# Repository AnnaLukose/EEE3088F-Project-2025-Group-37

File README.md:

# EEE3088F-Project-2025
Welcome to the repo for group 37's micromouse project!

The final design kicad files are available in the KICAD FILES folder.
Previous versions are also available in the draft 1 and draft 2 zip folders.

To view the schematic for our final design, view the Schematic pdf above.

This project required us to design a single PCB to fulfill the following power module requirements for a micromouse:

* Operate up to 4 motors bidirectionally with the pins available to you (listed in the power pinout
table). You will need to control 2x brushed DC motors which could each draw 200mA at the
highest voltage of a 1S1P battery (the battery is further specified in the battery section).
The other 2x motors are for the auxiliary connection and need to operate 500mA each.
* Place an INA219 for monitoring the battery on the I2C Bus and configure it correctly with
respect to the hardware (cannot have BOTH A0 AND A1 on GND)
* Charge the battery from the 9V input pin (listed in the power pinout table).
* Have two charging modes for a higher and lower charging current for the battery (200mA, and
approximately 600mA ±100mA from the battery perspective.
* Integrate USB C and get 9V out of the USB Host
* Provide 2x External Load Switching at 1A each (High Side connected to your 5V)
* Provide a 3V3 5% accuracy (300mA max) and 5V Out 5% accuracy (1.5A max)
* Provide an ON/OFF switch. OFF state: battery draw <30uA. ON state: can provide your robot
peak current of 2A. The switch needs to shut down 5V and 3V3

The requirements were split between us, each members files can be found under their corresponding name.

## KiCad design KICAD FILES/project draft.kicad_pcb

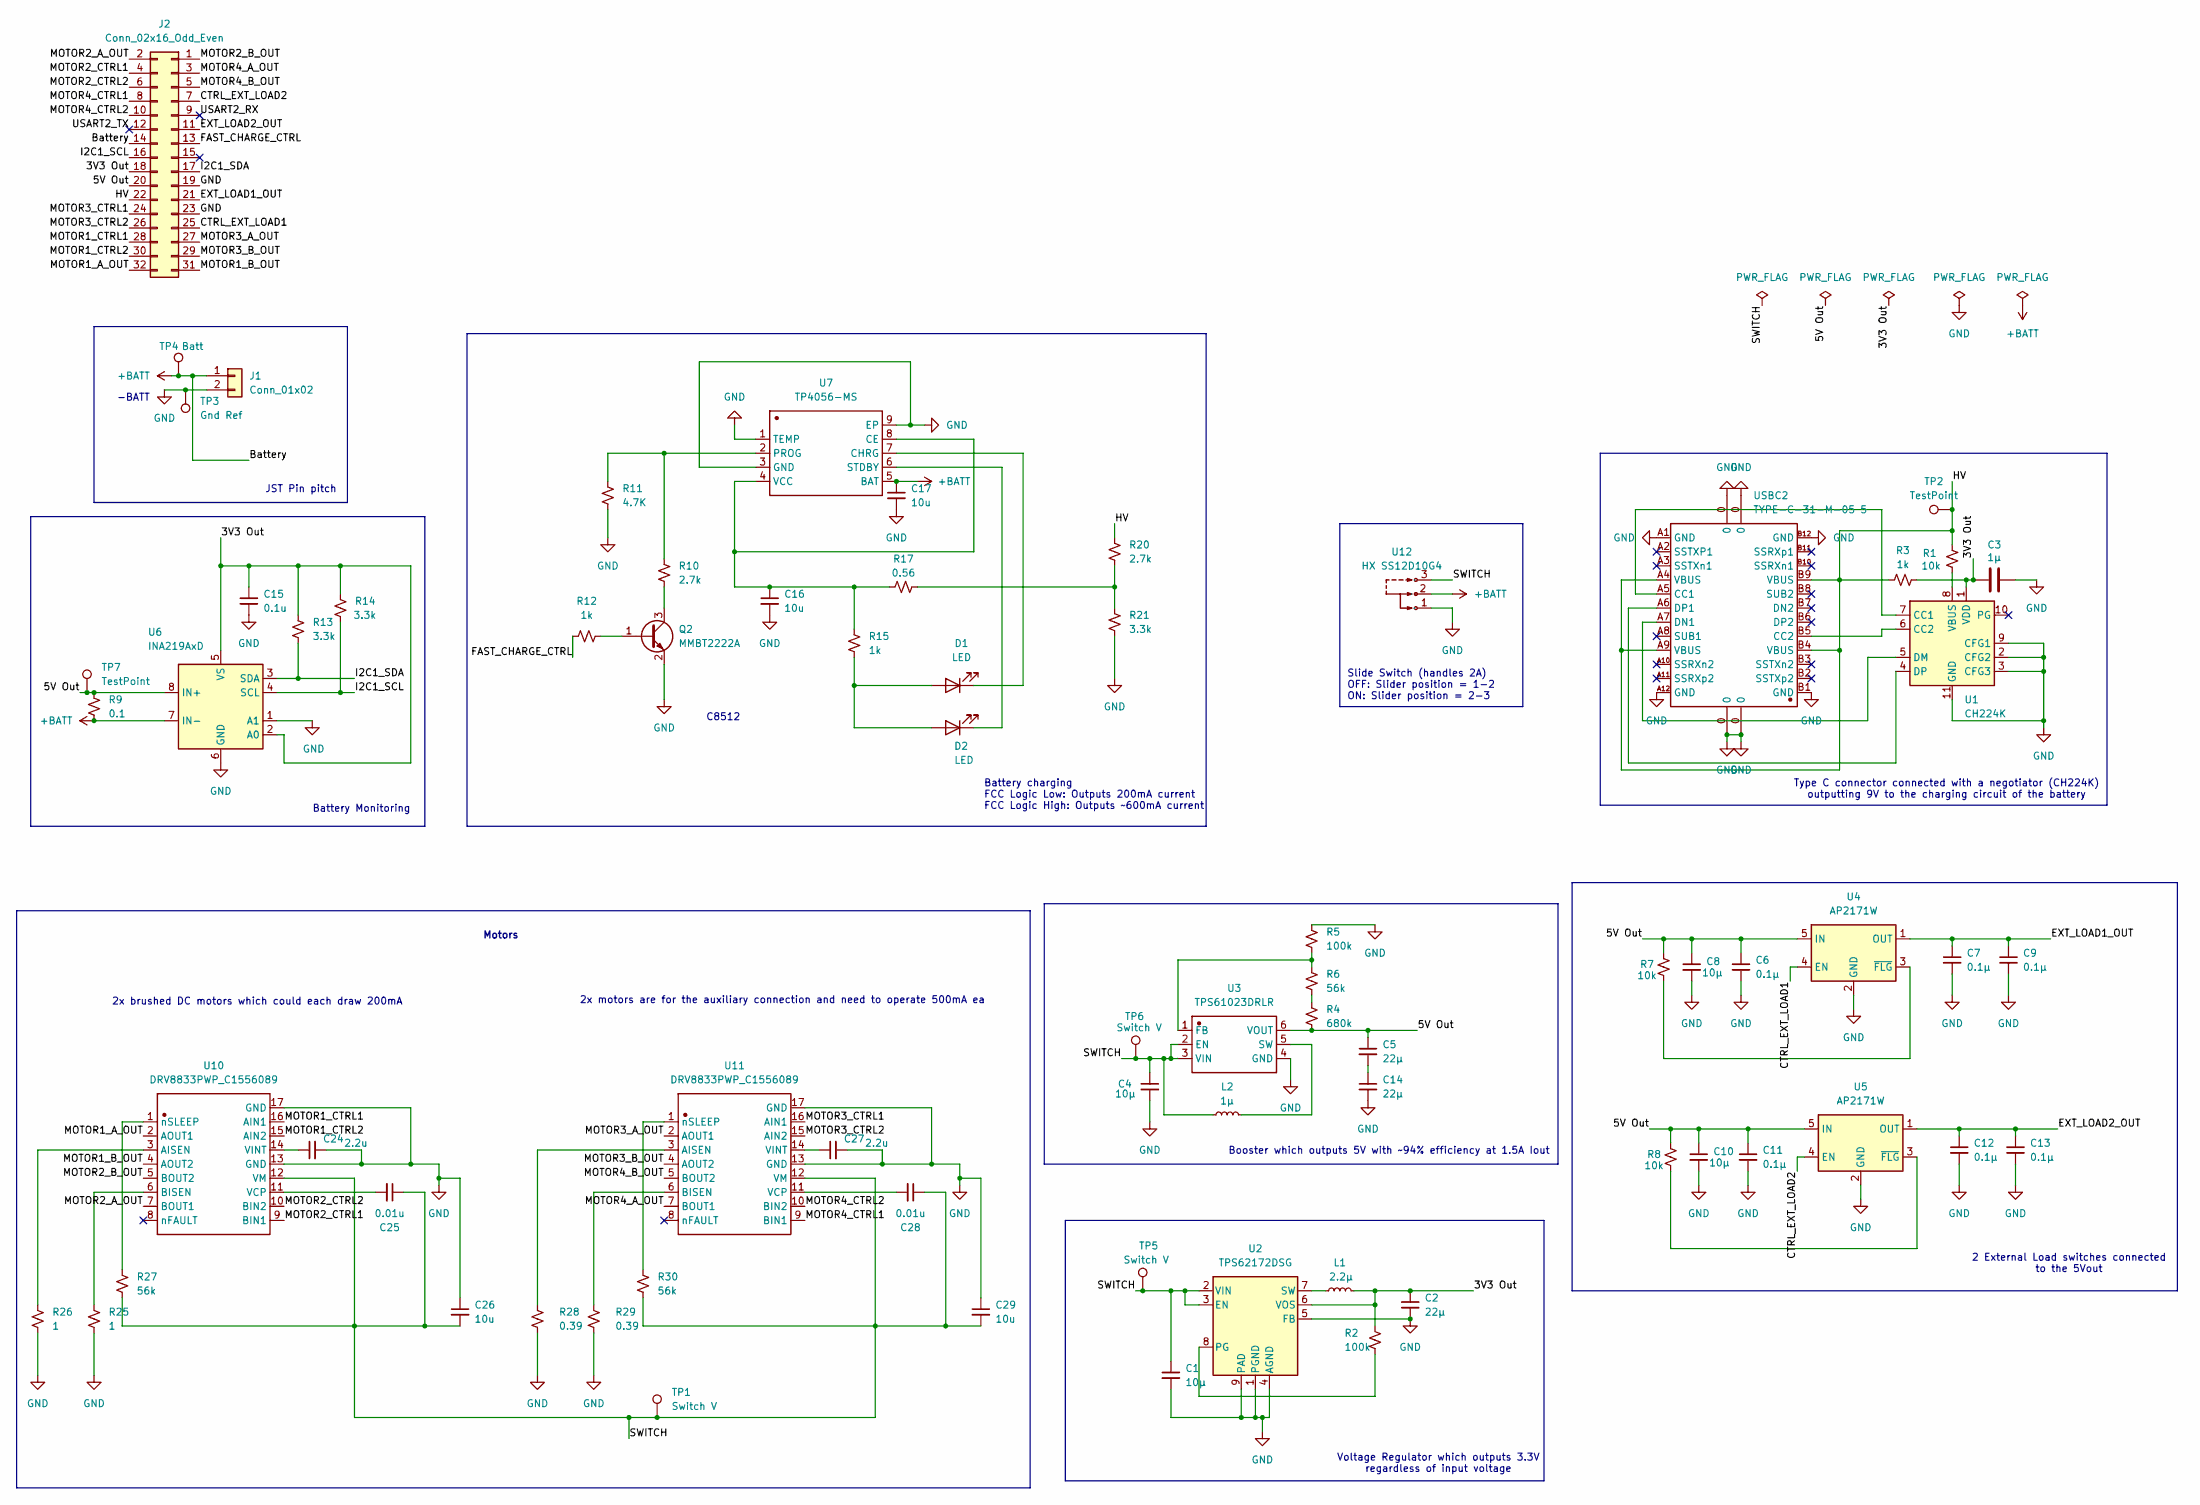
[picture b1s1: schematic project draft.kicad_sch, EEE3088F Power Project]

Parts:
C1: 10μ; C_01005_0402Metric_Pad0.57x0.30mm_HandSolder; LCSC C15525
C2, C5, C14: 22μ; C_0603_1608Metric_Pad1.08x0.95mm_HandSolder; LCSC C59461
C3: 1μ; C_0603_1608Metric_Pad1.08x0.95mm_HandSolder; LCSC C15849
C4, C8, C10: 10μ; C_0402_1005Metric_Pad0.74x0.62mm_HandSolder; LCSC C15525
C6, C7, C9, C11, C12, C13: 0.1μ; C_0402_1005Metric_Pad0.74x0.62mm_HandSolder; LCSC C1525
C15: 0.1u; C_0402_1005Metric_Pad0.74x0.62mm_HandSolder; LCSC C1525
C16, C17, C26, C29: 10u; C_0402_1005Metric_Pad0.74x0.62mm_HandSolder; LCSC C15525
C24, C27: 2.2u; C_0402_1005Metric_Pad0.74x0.62mm_HandSolder; LCSC C12530
C25, C28: 0.01u; C_0201_0603Metric_Pad0.64x0.40mm_HandSolder; LCSC C57112
D1: LED; LED_0603_1608Metric_Pad1.05x0.95mm_HandSolder; LCSC C2286
D2: LED; LED_0603_1608Metric_Pad1.05x0.95mm_HandSolder; LCSC C2290
J1: Conn_01x02; JST_PH_B2B-PH-K_1x02_P2.00mm_Vertical
J2: Conn_02x16_Odd_Even; PinSocket_2x16_P2.54mm_Vertical
L1: 2.2μ; L_0805_2012Metric_Pad1.05x1.20mm_HandSolder; LCSC C1043
L2: 1μ; L_0805_2012Metric_Pad1.05x1.20mm_HandSolder; LCSC C99367
Q2: MMBT2222A; SOT-23; LCSC C8512
R1, R7, R8: 10k; R_0603_1608Metric_Pad0.98x0.95mm_HandSolder; LCSC C25804
R2, R5: 100k; R_0603_1608Metric_Pad0.98x0.95mm_HandSolder; LCSC C25803
R3, R12, R15: 1k; R_0603_1608Metric_Pad0.98x0.95mm_HandSolder; LCSC C21190
R4: 680k; R_0402_1005Metric_Pad0.72x0.64mm_HandSolder; LCSC C4131
R6, R27, R30: 56k; R_0603_1608Metric_Pad0.98x0.95mm_HandSolder; LCSC C23206
R9: 0.1; R_0805_2012Metric_Pad1.20x1.40mm_HandSolder; LCSC C2934258
R10, R20: 2.7k; R_0603_1608Metric_Pad0.98x0.95mm_HandSolder; LCSC C13167
R11: 4.7K; R_0603_1608Metric_Pad0.98x0.95mm_HandSolder; LCSC C23162
R13, R14, R21: 3.3k; R_0603_1608Metric_Pad0.98x0.95mm_HandSolder; LCSC C22978
R17: 0.56; R_1206_3216Metric_Pad1.30x1.75mm_HandSolder; LCSC C2934309
R25, R26: 1; R_0603_1608Metric_Pad0.98x0.95mm_HandSolder; LCSC C22936
R28, R29: 0.39; R_0402_1005Metric_Pad0.72x0.64mm_HandSolder; LCSC C166621
TP1, TP5, TP6: Switch V; TestPoint_Pad_D2.0mm
TP2, TP7: TestPoint; TestPoint_Pad_D2.0mm
TP3: Gnd Ref; TestPoint_Pad_D2.0mm
TP4: Batt; TestPoint_Pad_D2.0mm
U1: CH224K; SSOP-10-1EP_3.9x4.9mm_P1mm_EP2.1x3.3mm; LCSC C970725
U2: TPS62172DSG; WSON-8-1EP_2x2mm_P0.5mm_EP0.9x1.6mm_ThermalVias; LCSC C59873
U3: TPS61023DRLR; SOT-563_L1.6-W1.2-P0.50-LS1.6-BR; Manufacturer Part TPS61023DRLR; LCSC C919459
U4, U5: AP2171W; SOT-23-5; LCSC C110466
U6: INA219AxD; SOIC-8_3.9x4.9mm_P1.27mm; LCSC C138706
U7: TP4056-MS; SOP-8_L4.9-W3.9-P1.27-LS6.0-TL-EP; Manufacturer Part TP4056-MS; LCSC C7473158
U10, U11: DRV8833PWP_C1556089; ETSSOP-16_L5.0-W4.4-P0.65-LS6.4-BL-EP; Manufacturer Part DRV8833PWP; LCSC C1556089
U12: HX SS12D10G4; SW-TH_SHOU-HAN_SS12D10G4; Manufacturer Part HX SS12D10G4; LCSC C5149841
USBC2: TYPE-C-31-M-05 5; TYPE-C-USB-23; Manufacturer Part TYPE-C-31-M-05; LCSC C845581

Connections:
+BATT: C17.1, J1.1, J2.14, R9.2, TP4.1, U6.7 (IN-), U7.5 (BAT), U12.2
/3V3 Out: C2.1, C3.1, C15.1, J2.18, L1.2, R2.1, R3.2, R13.1, R14.1, U1.1 (VDD), U2.6 (VOS), U6.2 (A0), U6.5 (VS)
/5V Out: C5.1, C6.1, C8.1, C10.1, C11.1, J2.20, R4.2, R7.1, R8.1, R9.1, TP7.1, U3.6 (VOUT), U4.5 (IN), U5.5 (IN), U6.8 (IN+)
/ USART2_RX: J2.9
/CTRL_EXT_LOAD1: J2.25, U4.4 (EN)
/CTRL_EXT_LOAD2: J2.7, U5.4 (EN)
/EXT_LOAD1_OUT: C7.1, C9.1, J2.21, U4.1 (OUT)
/EXT_LOAD2_OUT: C12.1, C13.1, J2.11, U5.1 (OUT)
/FAST_CHARGE_CTRL: J2.13, R12.1
/HV: J2.22, R1.2, R3.1, R20.1, TP2.1, USBC2.A4 (VBUS), USBC2.A9 (VBUS), USBC2.B4 (VBUS), USBC2.B9 (VBUS)
/I2C1_SCL: J2.16, R14.2, U6.4 (SCL)
/I2C1_SDA: J2.17, R13.2, U6.3 (SDA)
/MOTOR1_A_OUT: J2.32, U10.2 (AOUT1)
/MOTOR1_B_OUT: J2.31, U10.4 (AOUT2)
/MOTOR1_CTRL1: J2.28, U10.16 (AIN1)
/MOTOR1_CTRL2: J2.30, U10.15 (AIN2)
/MOTOR2_A_OUT: J2.2, U10.7 (BOUT1)
/MOTOR2_B_OUT: J2.1, U10.5 (BOUT2)
/MOTOR2_CTRL1: J2.4, U10.9 (BIN1)
/MOTOR2_CTRL2: J2.6, U10.10 (BIN2)
/MOTOR3_A_OUT: J2.27, U11.2 (AOUT1)
/MOTOR3_B_OUT: J2.29, U11.4 (AOUT2)
/MOTOR3_CTRL1: J2.24, U11.16 (AIN1)
/MOTOR3_CTRL2: J2.26, U11.15 (AIN2)
/MOTOR4_A_OUT: J2.3, U11.7 (BOUT1)
/MOTOR4_B_OUT: J2.5, U11.5 (BOUT2)
/MOTOR4_CTRL1: J2.8, U11.9 (BIN1)
/MOTOR4_CTRL2: J2.10, U11.10 (BIN2)
/SWITCH: C1.1, C4.1, C25.1, C26.2, C28.1, C29.2, L2.1, R27.2, R30.2, TP1.1, TP5.1, TP6.1, U2.2 (VIN), U2.3 (EN), U3.2 (EN), U3.3 (VIN), U10.12 (VM), U11.12 (VM), U12.3
/USART2_TX: J2.12
GND: C1.2, C2.2, C3.2, C4.2, C6.2, C7.2, C8.2, C9.2, C10.2, C11.2, C12.2, C13.2, C14.2, C15.2, C16.2, C17.2, C24.2, C26.1, C27.2, C29.1, J1.2, J2.19, J2.23, Q2.2 (E), R5.1, R11.2, R21.2, R25.2, R26.2, R28.2, R29.2, TP3.1, U1.2 (CFG2), U1.3 (CFG3), U1.9 (CFG1), U1.11 (GND), U2.1 (PGND), U2.4 (AGND), U2.5 (FB), U2.9 (PAD), U3.4 (GND), U4.2 (GND), U5.2 (GND), U6.1 (A1), U6.6 (GND), U7.1 (TEMP), U7.3 (GND), U7.9 (EP), U10.13 (GND), U10.17 (GND), U11.13 (GND), U11.17 (GND), U12.1, USBC2.0, USBC2.A1 (GND), USBC2.A12 (GND), USBC2.B1 (GND), USBC2.B12 (GND)
unnamed: C5.2, C14.1
unnamed: D1.2 (A), D2.2 (A), R15.1
unnamed: D1.1 (K), U7.7 (CHRG)
unnamed: D2.1 (K), U7.6 (STDBY)
unnamed: Q2.1 (B), R12.2
unnamed: Q2.3 (C), R10.2
unnamed: R4.1, R6.2
unnamed: R17.2, R20.2, R21.1
unnamed: U1.7 (CC1), USBC2.A5 (CC1)
unnamed: U1.6 (CC2), USBC2.B5 (CC2)
unnamed: U1.5 (DM), USBC2.A7 (DN1)
unnamed: U1.4 (DP), USBC2.A6 (DP1)
unnamed: R1.1, U1.8 (VBUS)
unnamed: R2.2, U2.8 (PG)
unnamed: L1.1, U2.7 (SW)
unnamed: R5.2, R6.1, U3.1 (FB)
unnamed: L2.2, U3.5 (SW)
unnamed: R7.2, U4.3 (~FLG)
unnamed: R8.2, U5.3 (~FLG)
unnamed: C16.1, R15.2, R17.1, U7.4 (VCC), U7.8 (CE)
unnamed: R10.1, R11.1, U7.2 (PROG)
unnamed: R26.1, U10.3 (AISEN)
unnamed: R25.1, U10.6 (BISEN)
unnamed: C25.2, U10.11 (VCP)
unnamed: C24.1, U10.14 (VINT)
unnamed: R27.1, U10.1 (nSLEEP)
unnamed: R28.1, U11.3 (AISEN)
unnamed: R29.1, U11.6 (BISEN)
unnamed: C28.2, U11.11 (VCP)
unnamed: C27.1, U11.14 (VINT)
unnamed: R30.1, U11.1 (nSLEEP)

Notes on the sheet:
2x motors are for the auxiliary connection and need to operate 500mA ea
Voltage Regulator which outputs 3.3V regardless of input voltage
2x brushed DC motors which could each draw 200mA
JST Pin pitch
Type C connector connected with a negotiator (CH224K) outputting 9V to the charging circuit of the battery
C8512
Battery Monitoring
Slide Switch (handles 2A) OFF: Slider position = 1-2 ON: Slider position = 2-3
2 External Load switches connected to the 5Vout
-BATT
Motors
Booster which outputs 5V with ~94% efficiency at 1.5A Iout
Battery charging FCC Logic Low: Outputs 200mA current FCC Logic High: Outputs ~600mA current

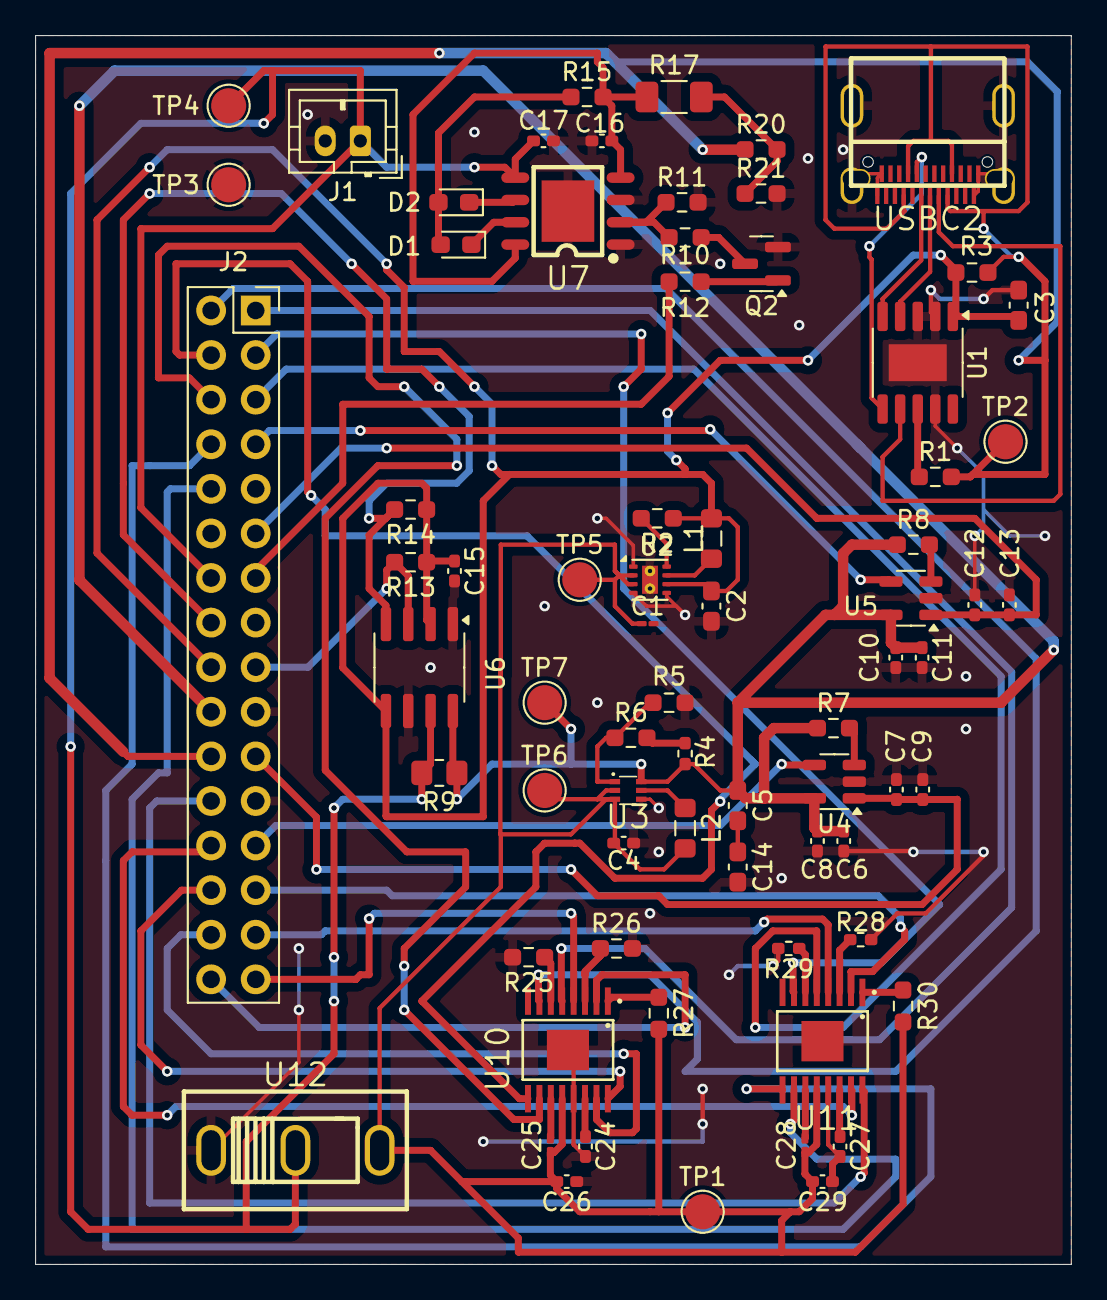
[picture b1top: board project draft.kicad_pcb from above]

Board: 2 copper layers, 59.0 x 70.0 mm, 72 parts (0 on the bottom side), 60 nets.

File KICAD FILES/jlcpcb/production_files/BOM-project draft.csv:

Comment,Designator,Footprint,LCSC,Quantity
2.2μ,L1,L_0805_2012Metric_Pad1.05x1.20mm_HandSolder,C1043,1
AP2171W,"U4,U5",SOT-23-5,C110466,2
2.2u,"C24,C27",C_0402_1005Metric_Pad0.74x0.62mm_HandSolder,C12530,2
2.7k,"R10,R20",R_0603_1608Metric_Pad0.98x0.95mm_HandSolder,C13167,2
INA219AxD,U6,SOIC-8_3.9x4.9mm_P1.27mm,C138706,1
0.1μ,"C11,C12,C13,C15,C6,C7,C9",C_0402_1005Metric_Pad0.74x0.62mm_HandSolder,C1525,7
10μ,"C1,C10,C16,C17,C26,C29,C4,C8",C_01005_0402Metric_Pad0.57x0.30mm_HandSolder,C15525,8
DRV8833PWP_C1556089,"U10,U11",ETSSOP-16_L5.0-W4.4-P0.65-LS6.4-BL-EP,C1556089,2
1μ,C3,C_0603_1608Metric_Pad1.08x0.95mm_HandSolder,C15849,1
0.39,"R28,R29",R_0402_1005Metric_Pad0.72x0.64mm_HandSolder,C166621,2
1k,"R12,R15,R3",R_0603_1608Metric_Pad0.98x0.95mm_HandSolder,C21190,3
LED,D1,LED_0603_1608Metric_Pad1.05x0.95mm_HandSolder,C2286,1
LED,D2,LED_0603_1608Metric_Pad1.05x0.95mm_HandSolder,C2290,1
1,"R25,R26",R_0603_1608Metric_Pad0.98x0.95mm_HandSolder,C22936,2
3.3k,"R13,R14,R21",R_0603_1608Metric_Pad0.98x0.95mm_HandSolder,C22978,3
4.7K,R11,R_0603_1608Metric_Pad0.98x0.95mm_HandSolder,C23162,1
56k,"R27,R30,R6",R_0603_1608Metric_Pad0.98x0.95mm_HandSolder,C23206,3
100k,"R2,R5",R_0603_1608Metric_Pad0.98x0.95mm_HandSolder,C25803,2
10k,"R1,R7,R8",R_0603_1608Metric_Pad0.98x0.95mm_HandSolder,C25804,3
0.1,R9,R_0805_2012Metric_Pad1.20x1.40mm_HandSolder,C2934258,1
0.56,R17,R_1206_3216Metric_Pad1.30x1.75mm_HandSolder,C2934309,1
680k,R4,R_0402_1005Metric_Pad0.72x0.64mm_HandSolder,C4131,1
HX SS12D10G4,U12,SW-TH_SHOU-HAN_SS12D10G4,C5149841,1
0.01u,"C25,C28",C_0201_0603Metric_Pad0.64x0.40mm_HandSolder,C57112,2
22μ,"C14,C2,C5",C_0603_1608Metric_Pad1.08x0.95mm_HandSolder,C59461,3
TPS62172DSG,U2,WSON-8-1EP_2x2mm_P0.5mm_EP0.9x1.6mm_ThermalVias,C59873,1
TP4056-MS,U7,SOP-8_L4.9-W3.9-P1.27-LS6.0-TL-EP,C7473158,1
TYPE-C-31-M-05 5,USBC2,TYPE-C-USB-23,C845581,1
MMBT2222A,Q2,SOT-23,C8512,1
TPS61023DRLR,U3,SOT-563_L1.6-W1.2-P0.50-LS1.6-BR,C919459,1
CH224K,U1,SSOP-10-1EP_3.9x4.9mm_P1mm_EP2.1x3.3mm,C970725,1
1μ,L2,L_0805_2012Metric_Pad1.05x1.20mm_HandSolder,C99367,1

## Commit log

2025-03-25 Update README.md on basic requirements
2025-03-25 Update README.md pinout
2025-04-21 Added schematic
2025-04-22 Added kicad files
2025-04-23 draft 1
2025-04-23 draft 2
2025-05-15 Added indiviual folders
2025-05-17 Update Anna folder
2025-05-17 Added LKSANN001 Schematic
